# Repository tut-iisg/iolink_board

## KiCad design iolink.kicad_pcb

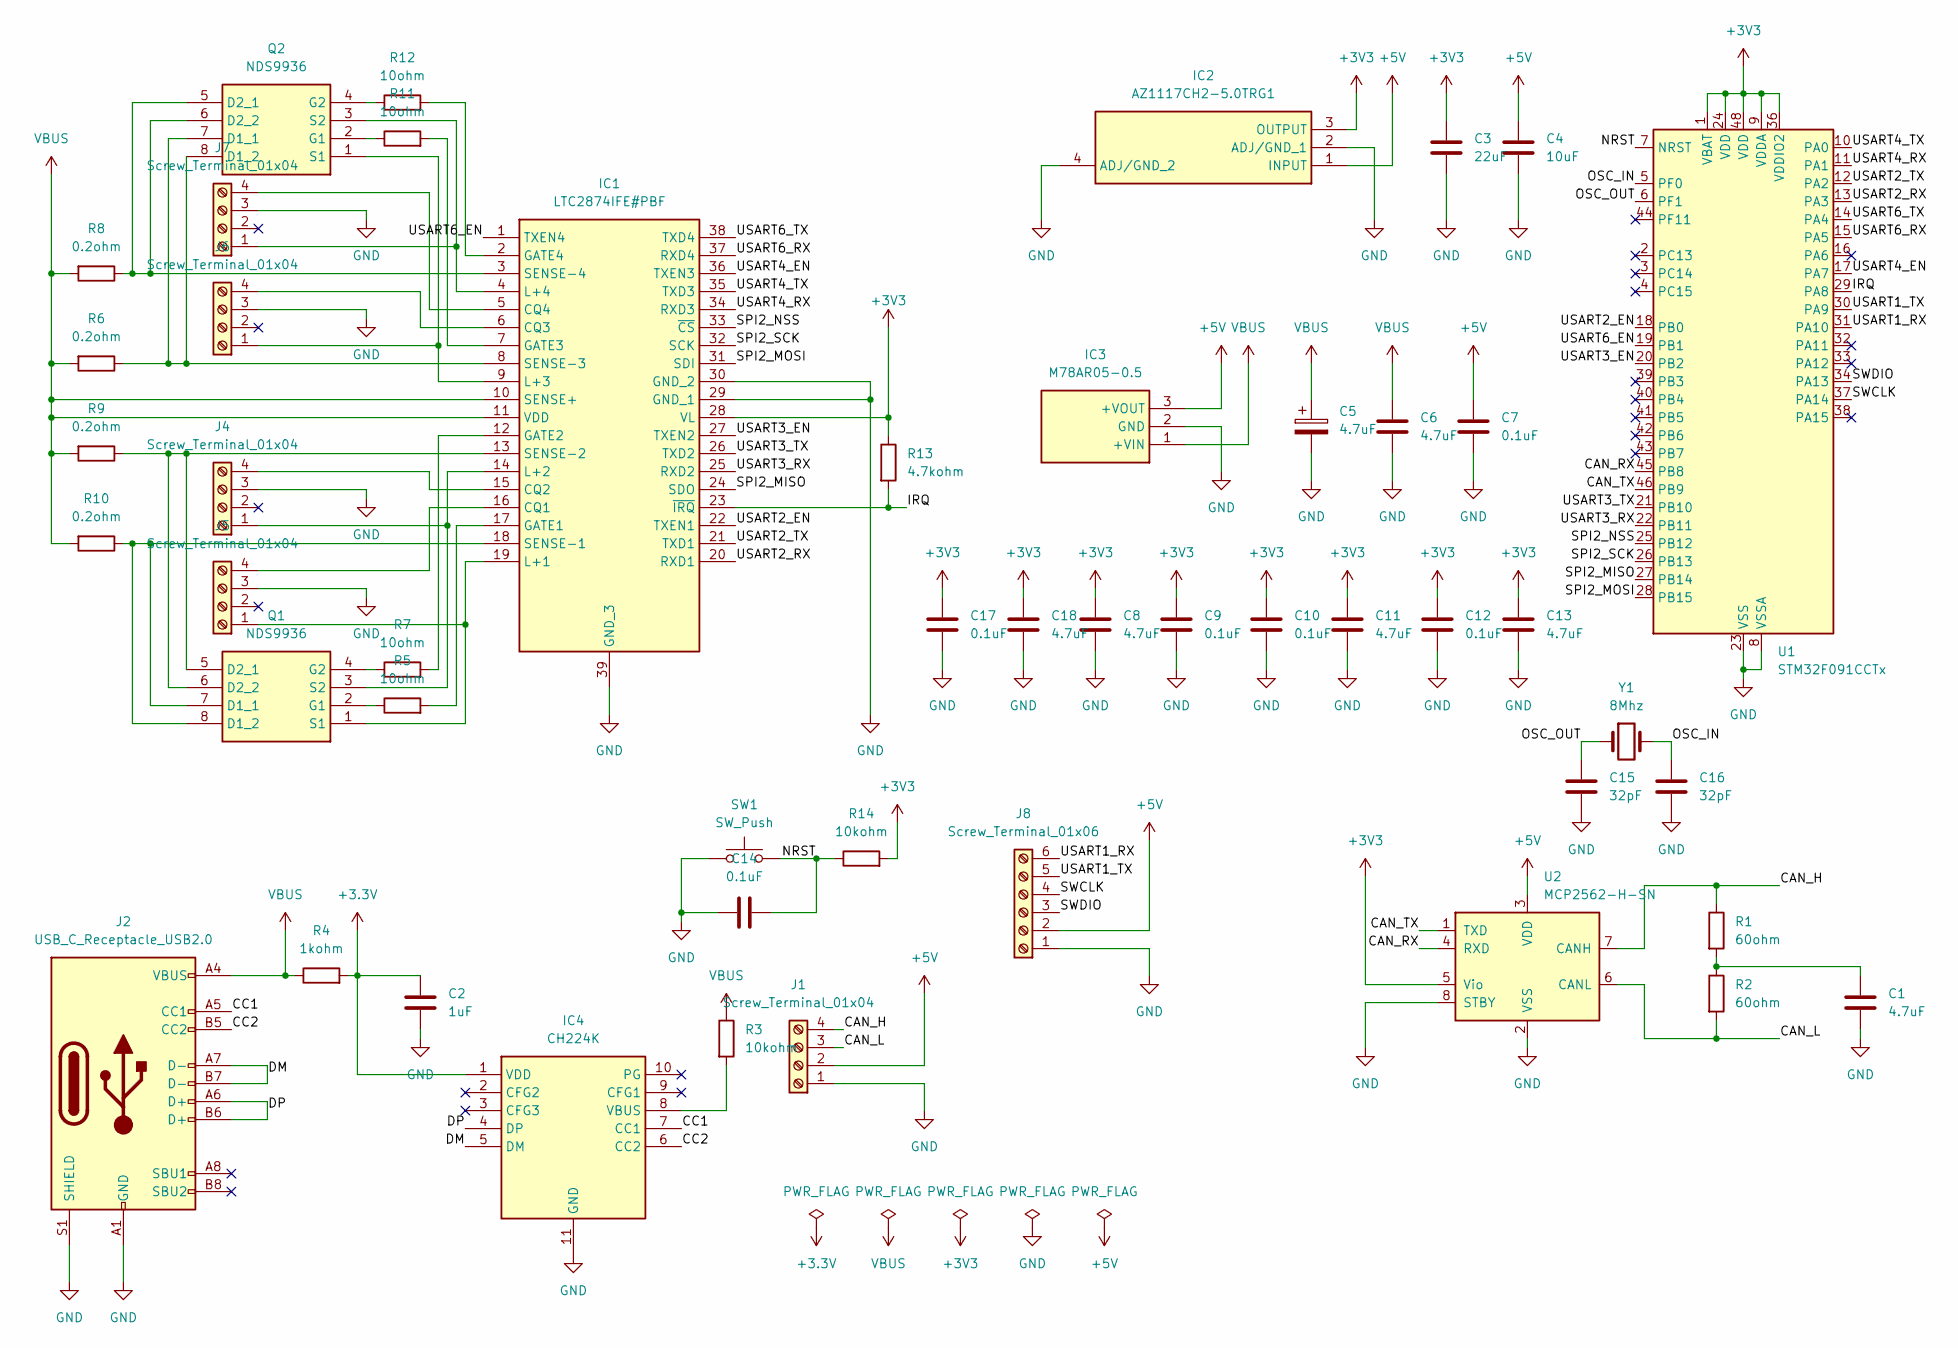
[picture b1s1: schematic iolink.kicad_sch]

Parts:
C1, C5, C6, C8, C11, C13, C18: 4.7uF; C_0603_1608Metric
C2: 1uF; C_0603_1608Metric
C3: 22uF; C_0603_1608Metric
C4: 10uF; C_0603_1608Metric
C7, C9, C10, C12, C14, C17: 0.1uF; C_0603_1608Metric
C15, C16: 32pF; C_0603_1608Metric
IC1: LTC2874IFE#PBF; SOP50P640X120-39N; Manufacturer_Part_Number LTC2874IFE#PBF; Mouser Part Number 584-LTC2874IFE#PBF
IC2: AZ1117CH2-5.0TRG1; SOT230P700X180-4N; Manufacturer_Part_Number AZ1117CH2-5.0TRG1; Mouser Part Number 621-AZ1117CH2-5.0TRG
IC3: M78AR05-0.5; M78AR05; Manufacturer_Part_Number M78AR05-0.5
IC4: CH224K; SOP100P600X180-11N; Manufacturer_Part_Number CH224K
J1, J4, J5, J6, J7: Screw_Terminal_01x04; TerminalBlock_Phoenix_MPT-0,5-4-2.54_1x04_P2.54mm_Horizontal
J2: USB_C_Receptacle_USB2.0; USB_C_Receptacle_GCT_USB4105-xx-A_16P_TopMnt_Horizontal
J8: Screw_Terminal_01x06; TerminalBlock_Phoenix_MPT-0,5-6-2.54_1x06_P2.54mm_Horizontal
Q1, Q2: NDS9936; SOIC127P600X175-8N; Manufacturer_Part_Number NDS9936; Mouser Part Number 512-NDS9936
R1, R2: 60ohm; R_0603_1608Metric
R3, R14: 10kohm; R_0603_1608Metric
R4: 1kohm; R_0603_1608Metric
R5, R7, R11, R12: 10ohm; R_0603_1608Metric
R6, R8, R9, R10: 0.2ohm; R_0603_1608Metric
R13: 4.7kohm; R_0603_1608Metric
SW1: SW_Push; SW_PUSH_6mm_H4.3mm
U1: STM32F091CCTx; LQFP-48_7x7mm_P0.5mm
U2: MCP2562-H-SN; SOIC-8_3.9x4.9mm_P1.27mm
Y1: 8Mhz; Crystal_HC52-8mm_Vertical

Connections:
+3.3V: C2.1, IC4.1 (VDD), R4.2
+3V3: C3.1, C8.1, C9.1, C10.1, C11.1, C12.1, C13.1, C17.1, C18.1, IC1.28 (VL), IC2.3 (OUTPUT), R13.1, R14.2, U1.1 (VBAT), U1.9 (VDDA), U1.24 (VDD), U1.36 (VDDIO2), U1.48 (VDD), U2.5 (Vio)
+5V: C4.1, C7.1, IC2.1 (INPUT), IC3.3 (+VOUT), J1.2, J8.2, U2.3 (VDD)
/CAN_H: J1.4, R1.1, U2.7 (CANH)
/CAN_L: J1.3, R2.2, U2.6 (CANL)
/CAN_RX: U1.45 (PB8), U2.4 (RXD)
/CAN_TX: U1.46 (PB9), U2.1 (TXD)
/CC1: IC4.7 (CC1), J2.A5 (CC1)
/CC2: IC4.6 (CC2), J2.B5 (CC2)
/DM: IC4.5 (DM), J2.A7 (D-), J2.B7 (D-)
/DP: IC4.4 (DP), J2.A6 (D+), J2.B6 (D+)
/IRQ: IC1.23 (~IRQ), R13.2, U1.29 (PA8)
/NRST: C14.2, R14.1, SW1.2, U1.7 (NRST)
/OSC_IN: C16.1, U1.5 (PF0), Y1.2
/OSC_OUT: C15.1, U1.6 (PF1), Y1.1
/SPI2_MISO: IC1.24 (SDO), U1.27 (PB14)
/SPI2_MOSI: IC1.31 (SDI), U1.28 (PB15)
/SPI2_NSS: IC1.33 (~CS), U1.25 (PB12)
/SPI2_SCK: IC1.32 (SCK), U1.26 (PB13)
/SWCLK: J8.4, U1.37 (PA14)
/SWDIO: J8.3, U1.34 (PA13)
/USART1_RX: J8.6, U1.31 (PA10)
/USART1_TX: J8.5, U1.30 (PA9)
/USART2_EN: IC1.22 (TXEN1), U1.18 (PB0)
/USART2_RX: IC1.20 (RXD1), U1.13 (PA3)
/USART2_TX: IC1.21 (TXD1), U1.12 (PA2)
/USART3_EN: IC1.27 (TXEN2), U1.20 (PB2)
/USART3_RX: IC1.25 (RXD2), U1.22 (PB11)
/USART3_TX: IC1.26 (TXD2), U1.21 (PB10)
/USART4_EN: IC1.36 (TXEN3), U1.17 (PA7)
/USART4_RX: IC1.34 (RXD3), U1.11 (PA1)
/USART4_TX: IC1.35 (TXD3), U1.10 (PA0)
/USART6_EN: IC1.1 (TXEN4), U1.19 (PB1)
/USART6_RX: IC1.37 (RXD4), U1.15 (PA5)
/USART6_TX: IC1.38 (TXD4), U1.14 (PA4)
GND: C1.1, C2.2, C3.2, C4.2, C5.2, C6.2, C7.2, C8.2, C9.2, C10.2, C11.2, C12.2, C13.2, C14.1, C15.2, C16.2, C17.2, C18.2, IC1.29 (GND_1), IC1.30 (GND_2), IC1.39 (GND_3), IC2.2 (ADJ/GND_1), IC2.4 (ADJ/GND_2), IC3.2 (GND), IC4.11 (GND), J1.1, J2.A1 (GND), J2.A12 (GND), J2.B1 (GND), J2.B12 (GND), J2.S1 (SHIELD), J4.3, J5.3, J6.3, J7.3, J8.1, SW1.1, U1.8 (VSSA), U1.23 (VSS), U1.35 (VSS), U1.47 (VSS), U2.2 (VSS), U2.8 (STBY)
unnamed: C1.2, R1.2, R2.1
unnamed: IC1.16 (CQ1), J5.4
unnamed: IC1.15 (CQ2), J4.4
unnamed: IC1.6 (CQ3), J6.4
unnamed: IC1.5 (CQ4), J7.4
unnamed: IC1.17 (GATE1), R5.2
unnamed: IC1.12 (GATE2), R7.2
unnamed: IC1.7 (GATE3), R11.2
unnamed: IC1.2 (GATE4), R12.2
unnamed: IC1.19 (L+1), J5.1, Q1.1 (S1)
unnamed: IC1.14 (L+2), J4.1, Q1.3 (S2)
unnamed: IC1.9 (L+3), J6.1, Q2.1 (S1)
unnamed: IC1.4 (L+4), J7.1, Q2.3 (S2)
unnamed: IC1.18 (SENSE-1), Q1.7 (D1_1), Q1.8 (D1_2), R10.1
unnamed: IC1.13 (SENSE-2), Q1.5 (D2_1), Q1.6 (D2_2), R9.1
unnamed: IC1.8 (SENSE-3), Q2.7 (D1_1), Q2.8 (D1_2), R6.1
unnamed: IC1.3 (SENSE-4), Q2.5 (D2_1), Q2.6 (D2_2), R8.1
unnamed: IC4.8 (VBUS), R3.2
unnamed: Q1.2 (G1), R5.1
unnamed: Q1.4 (G2), R7.1
unnamed: Q2.2 (G1), R11.1
unnamed: Q2.4 (G2), R12.1
VBUS: C5.1, C6.1, IC1.10 (SENSE+), IC1.11 (VDD), IC3.1 (+VIN), J2.A4 (VBUS), J2.A9 (VBUS), J2.B4 (VBUS), J2.B9 (VBUS), R3.1, R4.1, R6.2, R8.2, R9.2, R10.2

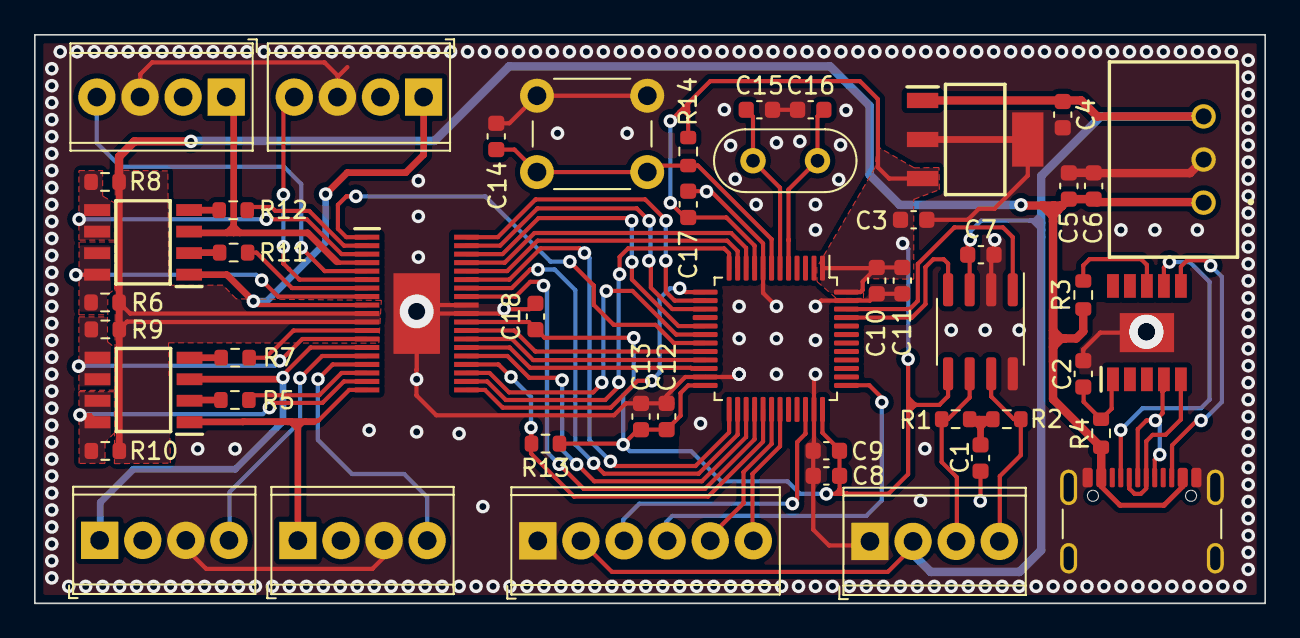
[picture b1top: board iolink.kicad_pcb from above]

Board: 2 copper layers, 72.5 x 33.5 mm, 49 parts (0 on the bottom side), 59 nets.

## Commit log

2024-01-13 schematic
2024-03-04 temp
2024-03-08 complete
